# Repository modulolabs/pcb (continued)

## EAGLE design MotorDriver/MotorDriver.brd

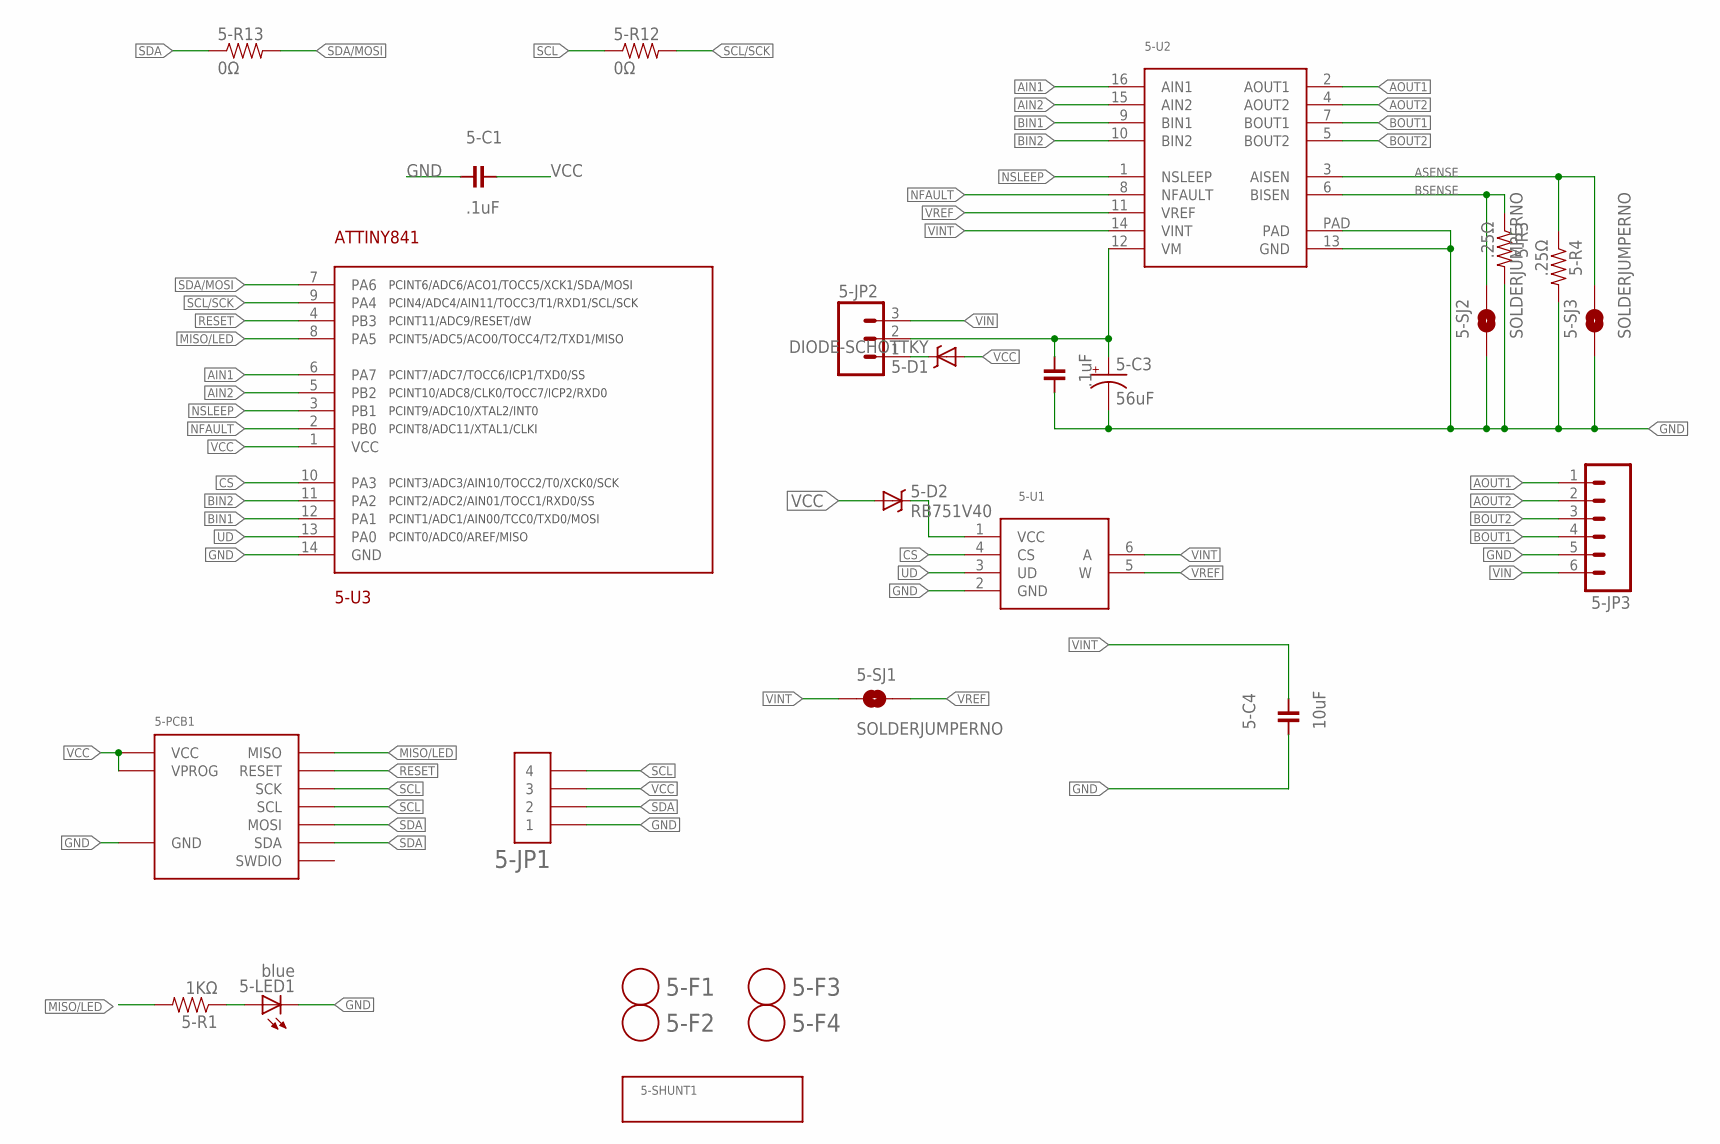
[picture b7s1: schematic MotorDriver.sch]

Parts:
5-C1: .1uF; 0603
5-C2: .1uF; 0603; RATING >20V
5-C3: 56uF; PANASONIC_D; RATING >20V
5-C4: 10uF; 0603
5-D1: DIODE-SCHOTTKY; SMP
5-D2: RB751V40; SOD-323; PARTNUM RB751V40
5-F1, 5-F2, 5-F3, 5-F4: FIDUCIAL; FIDUCIAL_1MM
5-JP1: HEADER-1X4-AMPMODU; AMPMODU-4P
5-JP2: M03LOCK_NO_SILK; 1X03_LOCK_NO_SILK; PARTNUM M20-9990346
5-JP3: M063.5MM-6; SCREWTERMINAL-3.5MM-6; PARTNUM OSTTE060104
5-LED1: blue; 0805-LED
5-PCB1: DEVICE-PCB; PARTNUM Motor Driver PCB
5-R1: 1KΩ; 0603
5-R3, 5-R4: .25Ω; R2010; PARTNUM CSRN2010FKR250
5-R12, 5-R13: 0Ω; 0603
5-SJ1, 5-SJ2, 5-SJ3: SOLDERJUMPERNO; SJ_2S-NO
5-U1: MCP4013; SOT-23-6
5-U2: DRV8848; HTSSOP-16
5-U3: ATTINY841; SOIC-14

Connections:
AIN1: 5-U2.16 (AIN1), 5-U3.6 (PA7)
AIN2: 5-U2.15 (AIN2), 5-U3.5 (PB2)
AOUT1: 5-JP3.1, 5-U2.2 (AOUT1)
AOUT2: 5-JP3.2, 5-U2.4 (AOUT2)
ASENSE: 5-R4.1, 5-SJ3.2, 5-U2.3 (AISEN)
BIN1: 5-U2.9 (BIN1), 5-U3.12 (PA1)
BIN2: 5-U2.10 (BIN2), 5-U3.11 (PA2)
BOUT1: 5-JP3.4, 5-U2.7 (BOUT1)
BOUT2: 5-JP3.3, 5-U2.5 (BOUT2)
BSENSE: 5-R3.1, 5-SJ2.2, 5-U2.6 (BISEN)
CS: 5-U1.4 (CS), 5-U3.10 (PA3)
GND: 5-C1.2, 5-C2.2, 5-C3.-, 5-C4.2, 5-JP1.P$1 (1), 5-JP1.P$2 (1), 5-JP3.5, 5-LED1.C, 5-PCB1.GND, 5-R3.2, 5-R4.2, 5-SJ2.1, 5-SJ3.1, 5-U1.2 (GND), 5-U2.13 (GND), 5-U2.PAD, 5-U3.14 (GND)
MISO/LED: 5-PCB1.MISO, 5-R1.2, 5-U3.8 (PA5)
unnamed: 5-D1.C, 5-JP2.1
unnamed: 5-D2.C, 5-U1.1 (VCC)
unnamed: 5-LED1.A, 5-R1.1
unnamed: 5-C2.1, 5-C3.+, 5-JP2.2, 5-U2.12 (VM)
NFAULT: 5-U2.8 (NFAULT), 5-U3.2 (PB0)
NSLEEP: 5-U2.1 (NSLEEP), 5-U3.3 (PB1)
RESET: 5-PCB1.RESET, 5-U3.4 (PB3)
SCL: 5-JP1.P$7 (4), 5-JP1.P$8 (4), 5-PCB1.CLK (SCK), 5-PCB1.SCL, 5-R12.1
SCL/SCK: 5-R12.2, 5-U3.9 (PA4)
SDA: 5-JP1.P$3 (2), 5-JP1.P$4 (2), 5-PCB1.MOSI, 5-PCB1.SDA, 5-R13.1
SDA/MOSI: 5-R13.2, 5-U3.7 (PA6)
UD: 5-U1.3 (UD), 5-U3.13 (PA0)
VCC: 5-C1.1, 5-D1.A, 5-D2.A, 5-JP1.P$5 (3), 5-JP1.P$6 (3), 5-PCB1.VCC, 5-PCB1.VPROG, 5-U3.1 (VCC)
VIN: 5-JP2.3, 5-JP3.6
VINT: 5-C4.1, 5-SJ1.1, 5-U1.6 (A), 5-U2.14 (VINT)
VREF: 5-SJ1.2, 5-U1.5 (W), 5-U2.11 (VREF)

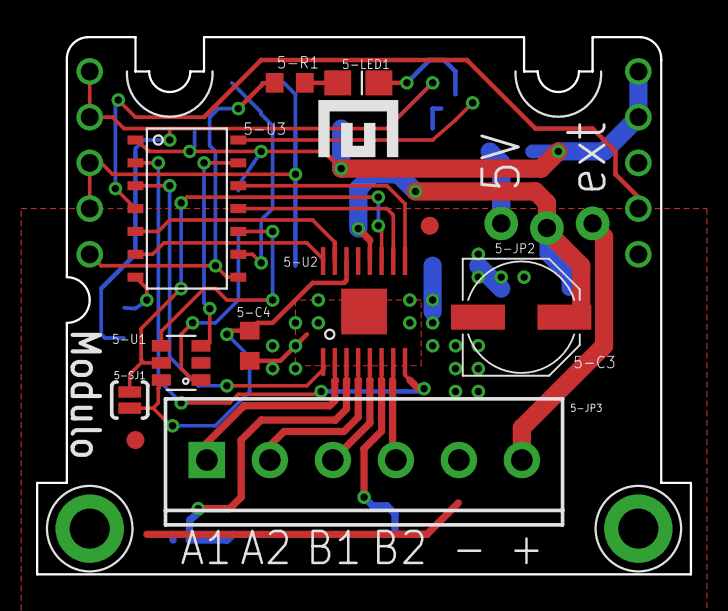
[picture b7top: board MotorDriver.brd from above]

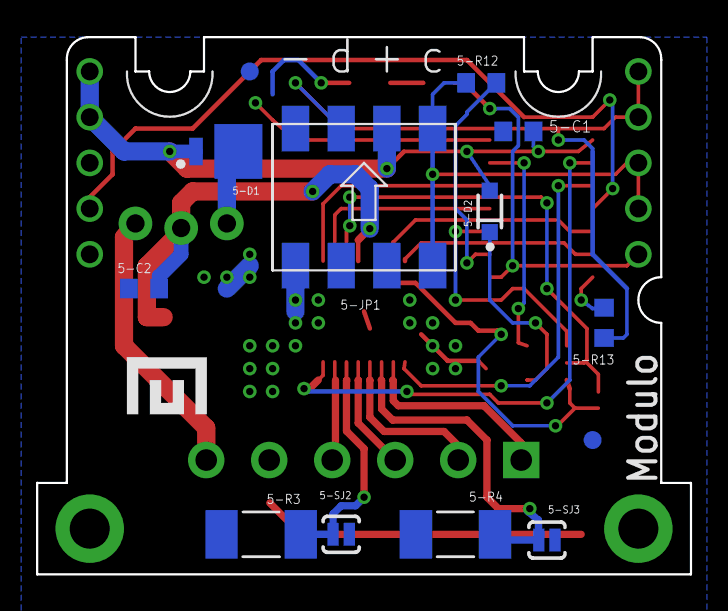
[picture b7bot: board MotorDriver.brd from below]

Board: 2 copper layers, 36.3 x 29.8 mm, 28 parts (14 on the bottom side), 29 nets.

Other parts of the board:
U$1, U$2: LOGO-SMALL

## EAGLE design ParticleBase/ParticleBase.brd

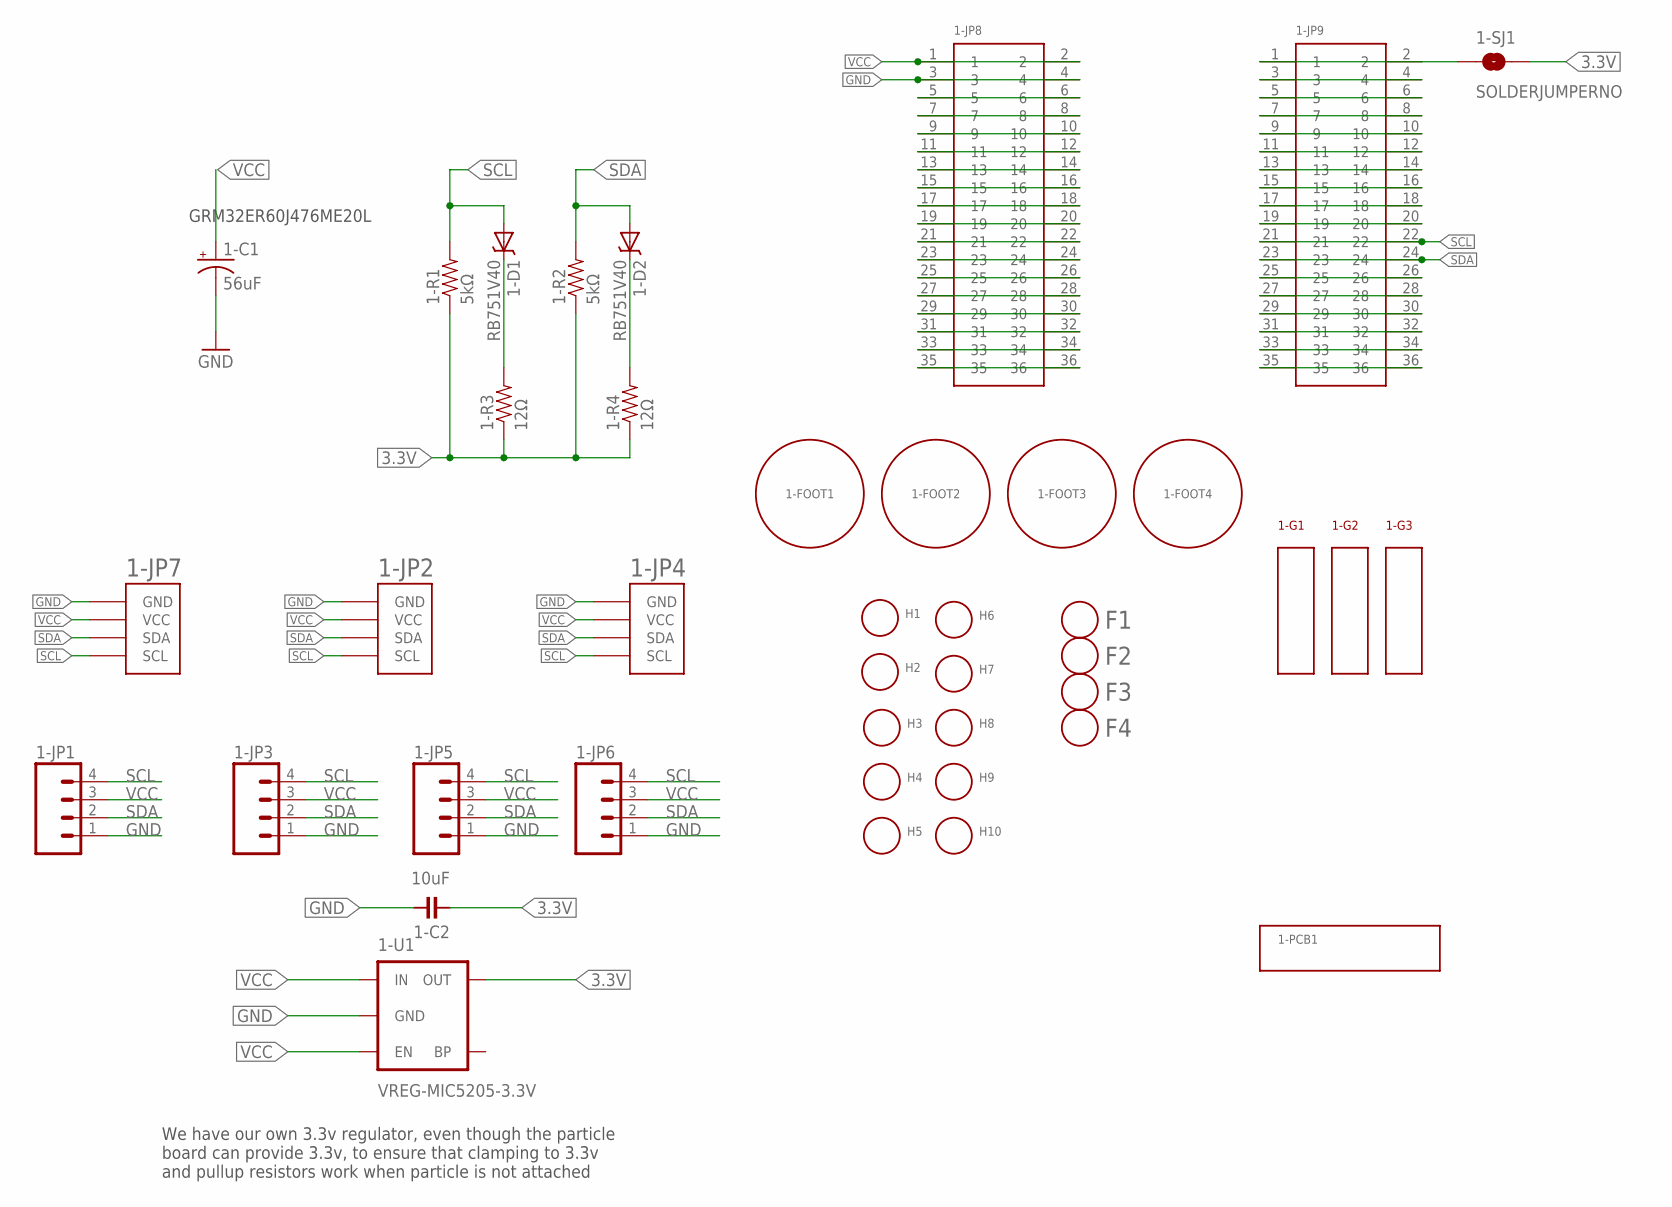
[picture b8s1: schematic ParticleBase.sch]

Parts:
1-C1: 56uF; PANASONIC_D
1-C2: 10uF; 0603
1-D1, 1-D2: RB751V40; SOD-323; PARTNUM RB751V40
1-FOOT1, 1-FOOT2, 1-FOOT3, 1-FOOT4: FOOT
1-G1, 1-G3: CARD-GUIDE; CARD-GUIDE-2; PARTNUM HCG-201-165
1-G2: CARD-GUIDE; CARD-GUIDE-2; PARTNUM HCG-202-165
1-JP1, 1-JP3, 1-JP5, 1-JP6: M04LOCK; 1X04_LOCK; PARTNUM M20-9750446
1-JP2, 1-JP4, 1-JP7: HEADER-MODULO; JST-PA-SIDE-SMD
1-JP8, 1-JP9: HEADER-2X18; 2X18-LOCK; PARTNUM 12x2 Receptacle
1-R1, 1-R2: 5kΩ; 0603
1-R3, 1-R4: 12Ω; 0603
1-SJ1: SOLDERJUMPERNO; SJ_2S-NO
1-U1: VREG-MIC5205-3.3V; SOT23-5
F1, F2, F3, F4: FIDUCIAL; FIDUCIAL_1MM
H1, H2, H3, H4, H5, H6, H7, H8, H9, H10: HOLE#2; HOLE-#2

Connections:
3.3V: 1-C2.2, 1-R1.1, 1-R2.1, 1-R3.1, 1-R4.1, 1-SJ1.2, 1-U1.5 (OUT)
GND: 1-C1.-, 1-C2.1, 1-JP1.1, 1-JP2.1 (GND), 1-JP3.1, 1-JP4.1 (GND), 1-JP5.1, 1-JP6.1, 1-JP7.1 (GND), 1-JP8.3, 1-JP8.4, 1-U1.2 (GND)
unnamed: 1-JP8.5, 1-JP8.6
unnamed: 1-JP8.7, 1-JP8.8
unnamed: 1-JP8.9, 1-JP8.10
unnamed: 1-JP8.11, 1-JP8.12
unnamed: 1-JP8.13, 1-JP8.14
unnamed: 1-JP8.15, 1-JP8.16
unnamed: 1-JP8.17, 1-JP8.18
unnamed: 1-JP8.19, 1-JP8.20
unnamed: 1-JP8.21, 1-JP8.22
unnamed: 1-JP8.23, 1-JP8.24
unnamed: 1-JP8.25, 1-JP8.26
unnamed: 1-JP8.27, 1-JP8.28
unnamed: 1-JP8.29, 1-JP8.30
unnamed: 1-JP9.5, 1-JP9.6
unnamed: 1-JP8.31, 1-JP8.32
unnamed: 1-D1.C, 1-R3.2
unnamed: 1-JP8.33, 1-JP8.34
unnamed: 1-JP8.35, 1-JP8.36
unnamed: 1-D2.C, 1-R4.2
unnamed: 1-JP9.3, 1-JP9.4
unnamed: 1-JP9.7, 1-JP9.8
unnamed: 1-JP9.9, 1-JP9.10
unnamed: 1-JP9.11, 1-JP9.12
unnamed: 1-JP9.13, 1-JP9.14
unnamed: 1-JP9.15, 1-JP9.16
unnamed: 1-JP9.17, 1-JP9.18
unnamed: 1-JP9.19, 1-JP9.20
unnamed: 1-JP9.25, 1-JP9.26
unnamed: 1-JP9.27, 1-JP9.28
unnamed: 1-JP9.29, 1-JP9.30
unnamed: 1-JP9.31, 1-JP9.32
unnamed: 1-JP9.33, 1-JP9.34
unnamed: 1-JP9.35, 1-JP9.36
unnamed: 1-JP9.1, 1-JP9.2, 1-SJ1.1
SCL: 1-D1.A, 1-JP1.4, 1-JP2.4 (SCL), 1-JP3.4, 1-JP4.4 (SCL), 1-JP5.4, 1-JP6.4, 1-JP7.4 (SCL), 1-JP9.21, 1-JP9.22, 1-R1.2
SDA: 1-D2.A, 1-JP1.2, 1-JP2.3 (SDA), 1-JP3.2, 1-JP4.3 (SDA), 1-JP5.2, 1-JP6.2, 1-JP7.3 (SDA), 1-JP9.23, 1-JP9.24, 1-R2.2
VCC: 1-C1.+, 1-JP1.3, 1-JP2.2 (VCC), 1-JP3.3, 1-JP4.2 (VCC), 1-JP5.3, 1-JP6.3, 1-JP7.2 (VCC), 1-JP8.1, 1-JP8.2, 1-U1.1 (IN), 1-U1.3 (EN)

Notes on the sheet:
GRM32ER60J476ME20L
We have our own 3.3v regulator, even though the particle board can provide 3.3v, to ensure that clamping to 3.3v and pullup resistors work when particle is not attached

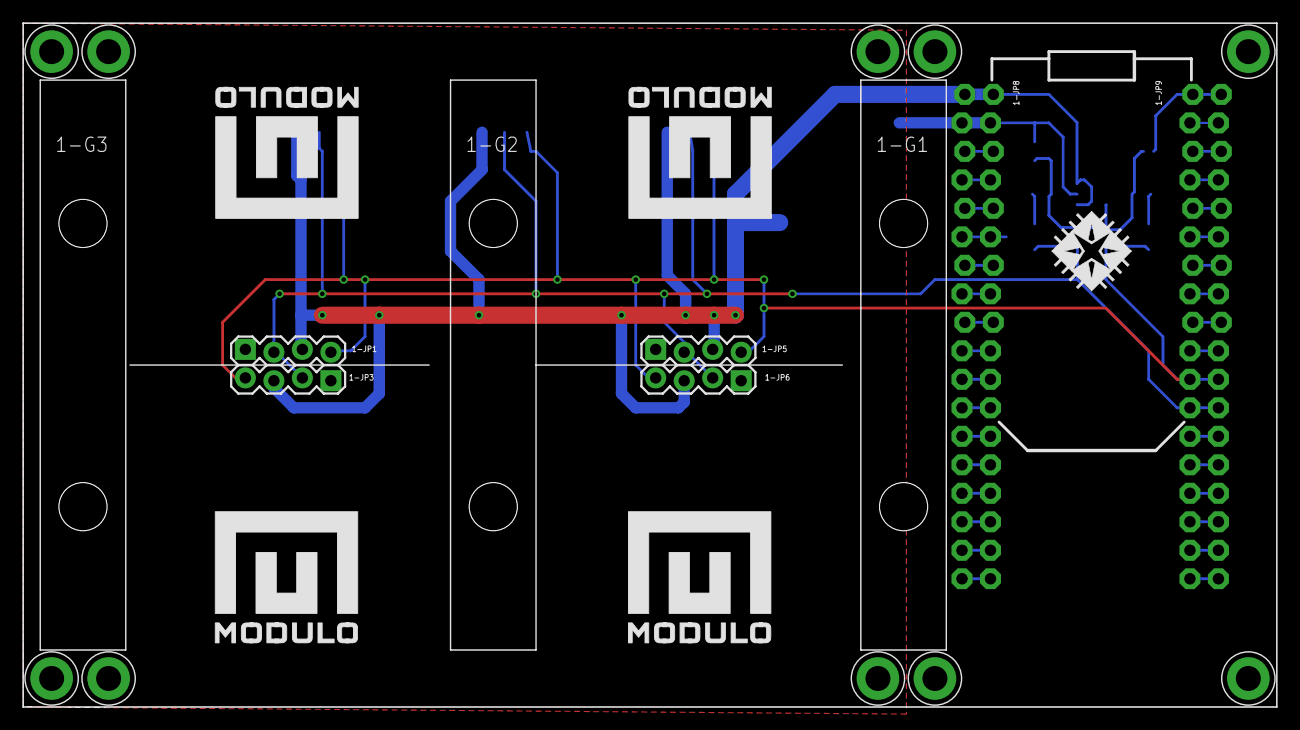
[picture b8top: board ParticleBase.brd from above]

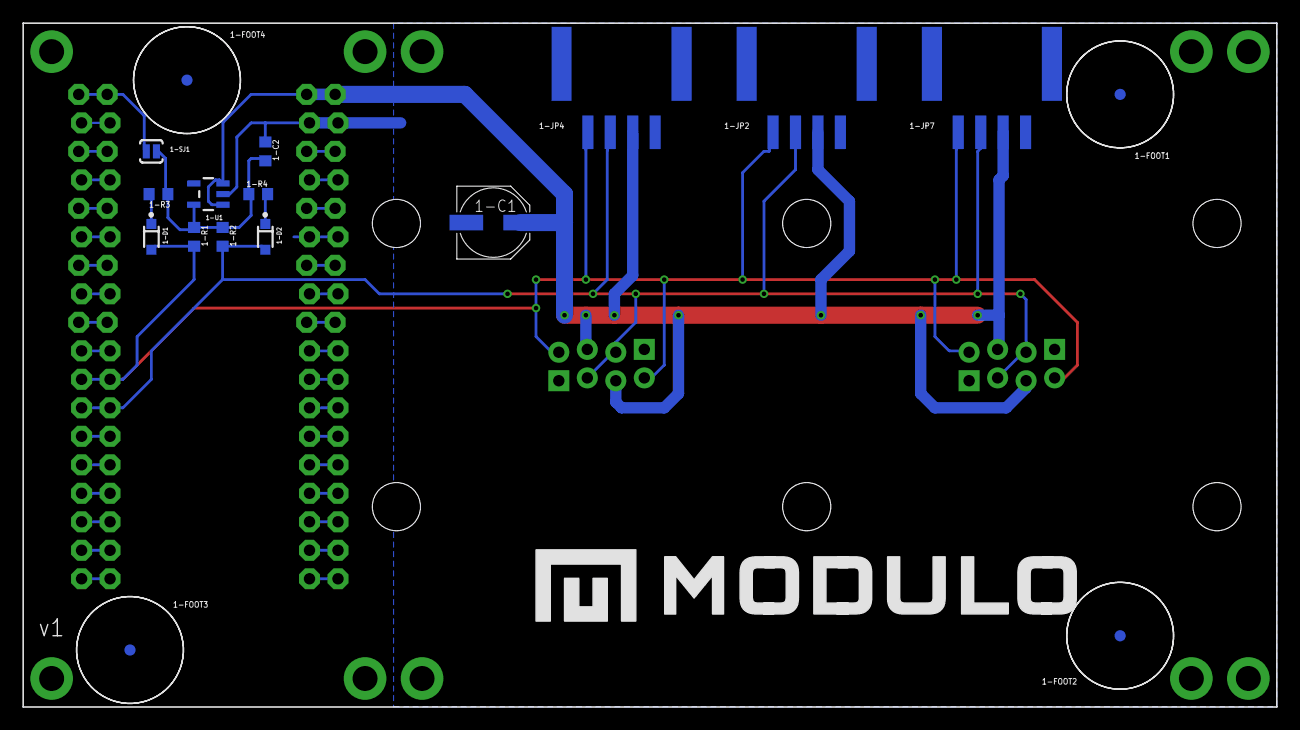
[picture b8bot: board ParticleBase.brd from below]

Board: 2 copper layers, 111.8 x 61.0 mm, 46 parts (22 on the bottom side), 39 nets.

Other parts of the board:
U$1, U$2, U$3, U$4: LOGO-0.5
U$5: LOGO-HOR-0.25
U$6: WORKS_WITH_PARTICLE_LOGO_LARGE

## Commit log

2014-06-20 Initial versions of a bunch of boards
2014-08-20 Checking in current version of OLED board
2014-08-22 New motor module
2014-08-22 GPIO board rebuilt for v2 footprint
2014-08-27 Added current limiting resistors to io pins
2014-08-30 Ruggedized GPIO board with current limiting resistors and clamping diodes.
2014-08-30 New OLED design for v2 footprint.
2014-08-30 New programmer/hub board with guide rails for v2 footprint.
2014-08-30 New motor driver board based on the NJM2670 chip.
2014-08-30 New arduino leonardo compatible board based on the ATmega32u4.
2014-08-30 BitButton board which works with the SparkFun elastomer button pad
2014-08-30 Mostly re-routed the TB6612FNG based motor driver board for the v2 footprint. Not finished, since I'm planning to abandon this chip.
2014-08-30 Latest version of NavButtons
2014-08-30 The integer labs eagle library. Copies of the SparkFun and adafruit libraries. Sunstone cam and dru files.
2014-08-30 Microcontroller board for the SAMD21 chip.
2014-08-30 Dual thermocouple module.
2014-08-30 Small thermistor board. Doesn't use modulo footprint, but instead is designed to be an inline/remote sensor.
2014-08-30 Cleaned up pcb repository file structure.
2014-09-08 Changed OLED board to use ATmega328P instead of ATtiny841.
2014-10-09 Latest controller revision
2014-10-15 Latest version of schematics and boards
2014-11-22 Changed NavButtons back to using attiny441
2014-11-22 New linear/inline layout of motor driver board
2014-11-22 Reverted to old version of motor driver board
2014-11-24 OLED: added buttons and rewired for attiny841 Thermocouple: checkpoint of latest version with two amplifiers and attiny48
2014-11-25 New thermocouple revision with single input and quick connect terminals
2014-11-25 Changed to use attiny841
2014-11-25 minor revisions
2014-11-25 Various changes to support recent commits
2014-12-22 New 32u4 controller board with servo pin compatible gpio and RPi reverse current protection.
2014-12-22 New Hub with smaller form factor and bus connectors on bottom.
2014-12-22 Updated footprint and swich, instead of jumper, for selecting output voltage.
2014-12-22 Switched to attiny841 and made the battery insert from the side.
2014-12-22 New versions of IntegerLabs library, RotaryEncoder, and Thermocouple
2014-12-22 New programmer board
2014-12-22 New switching power supply board
2014-12-22 New Raspberry Pi Adapter Board
2014-12-23 various minor changes
2015-04-02 Checkpointing PCB designs
2015-06-10 Various updates
2015-06-10 Renamed 32u4 to Controller
2015-06-10 Added OSHPark CAM scripts
2015-06-10 Created grid layout
2015-06-10 tag connect library
2015-06-10 Moved a bunch of files around
2015-07-09 Major revision of all boards. Cleaned up old files. Exported BOM csv files for all boards
2015-07-09 Part details spread sheet and script to consolidate BOMs for all boards into a single BOM.
2015-07-09 Design checklist spreadsheet
2015-07-10 New diode selections
2015-07-10 Minor changes
2015-07-22 Added knob cap BOM item
2015-07-22 Switched to side entry connectors
2015-07-28 Fixed a missing connection.
2015-08-15 New scripts that combine and panelize boards, boms, and centroid data.
2015-08-15 Revised temperature probe layout and created new temp probe programmer board
2015-08-15 Fixed bad clamp diode wiring and added a reverse protection diode
2015-08-15 Check point of current PCB designs. Among other things I think this change includes rewiring of programming lines on many of the boards,.
2015-08-18 Fixed missing trace on SCL/SCK net.
2015-08-19 Added parallel resistor on red channel for better white balance. Moved status LED to opposite side of the board next to logo Updated to new 0603 footprint.
2015-08-19 Added 3.3V regulator and solder jump to select operating voltage 10mil traces instead of 8 swapped I/O pins 3 and 4 so that PWM capable pins are contiguous moved the status LED so that it's next to t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
2015-08-19 Increased trace width to 10mil from 8 Bumped version number to 6
2015-08-19 Moved logo near LED Bumped version number Increased trace widths from 8mil to 10mil tented vias
2015-08-19 Updated to new 0603 and 0805 footprints
2015-08-20 Fixed 3.3V connection. The old pin worked with the Spark but not the Photon.
2015-08-20 Changed the JST-PA-SIDE-SMD package so that it also works with the Grove SMD connector Added new symbol for Modulo Header
2015-08-20 New DRU with tented vias
2015-08-20 New Grove compatible connector footprint
2015-08-20 Updated to grove compatible connector footprints
2015-08-20 Changed to use Grove connector
2015-08-21 Changed to use direct wire soldering for modulo bus instead of a connector.
2015-09-07 Updates to the Modulo eagle library
2015-09-07 Updated the readme file and assign an open source license.
2015-09-07 Tented vias Updated extension cable connectors Added 3.3v regulator and clamping diodes
2015-09-07 Fixed PARTNUM on 3.3v regulator.
2015-09-07 Various fixes
2015-09-07 Library update
2015-09-07 Various changes
2015-09-07 Moved panelization scripts into a separate repository
2015-09-07 Removed obsolete BOM files
2015-09-07 Created new library containing the "works with particle" logo
2015-09-07 Removed old unused files
2015-09-07 Removed unnecessary files
2015-09-07 Added a copy of particle's eagle library
2015-09-07 Added new Modulo CAM file with tented vias
2015-09-07 Added bom and centroid csv files
2015-09-07 Added topplace and bottomplace eps files
2015-09-11 Various small tweaks based on testing and feedback from manufacturer.
2015-09-17 Various minor tweaks based on testing and feedback from manufacturer
2015-09-17 New fiducial "board" for use by the panelization script
2015-10-07 Added unique board prefixes to part numbers due to CM requirements
2017-04-09 New thermocouple board.
2018-09-04 updated cam for Eagle 9 exported files for BlankSlate removed unused files '
2018-09-04 Exported cam data for Base and Joystick
2018-09-05 update specs and readme
2018-09-10 add rfq zips
